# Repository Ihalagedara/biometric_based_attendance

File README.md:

# biometric_based_attendance_web_page
Open the main.html file to view the web page

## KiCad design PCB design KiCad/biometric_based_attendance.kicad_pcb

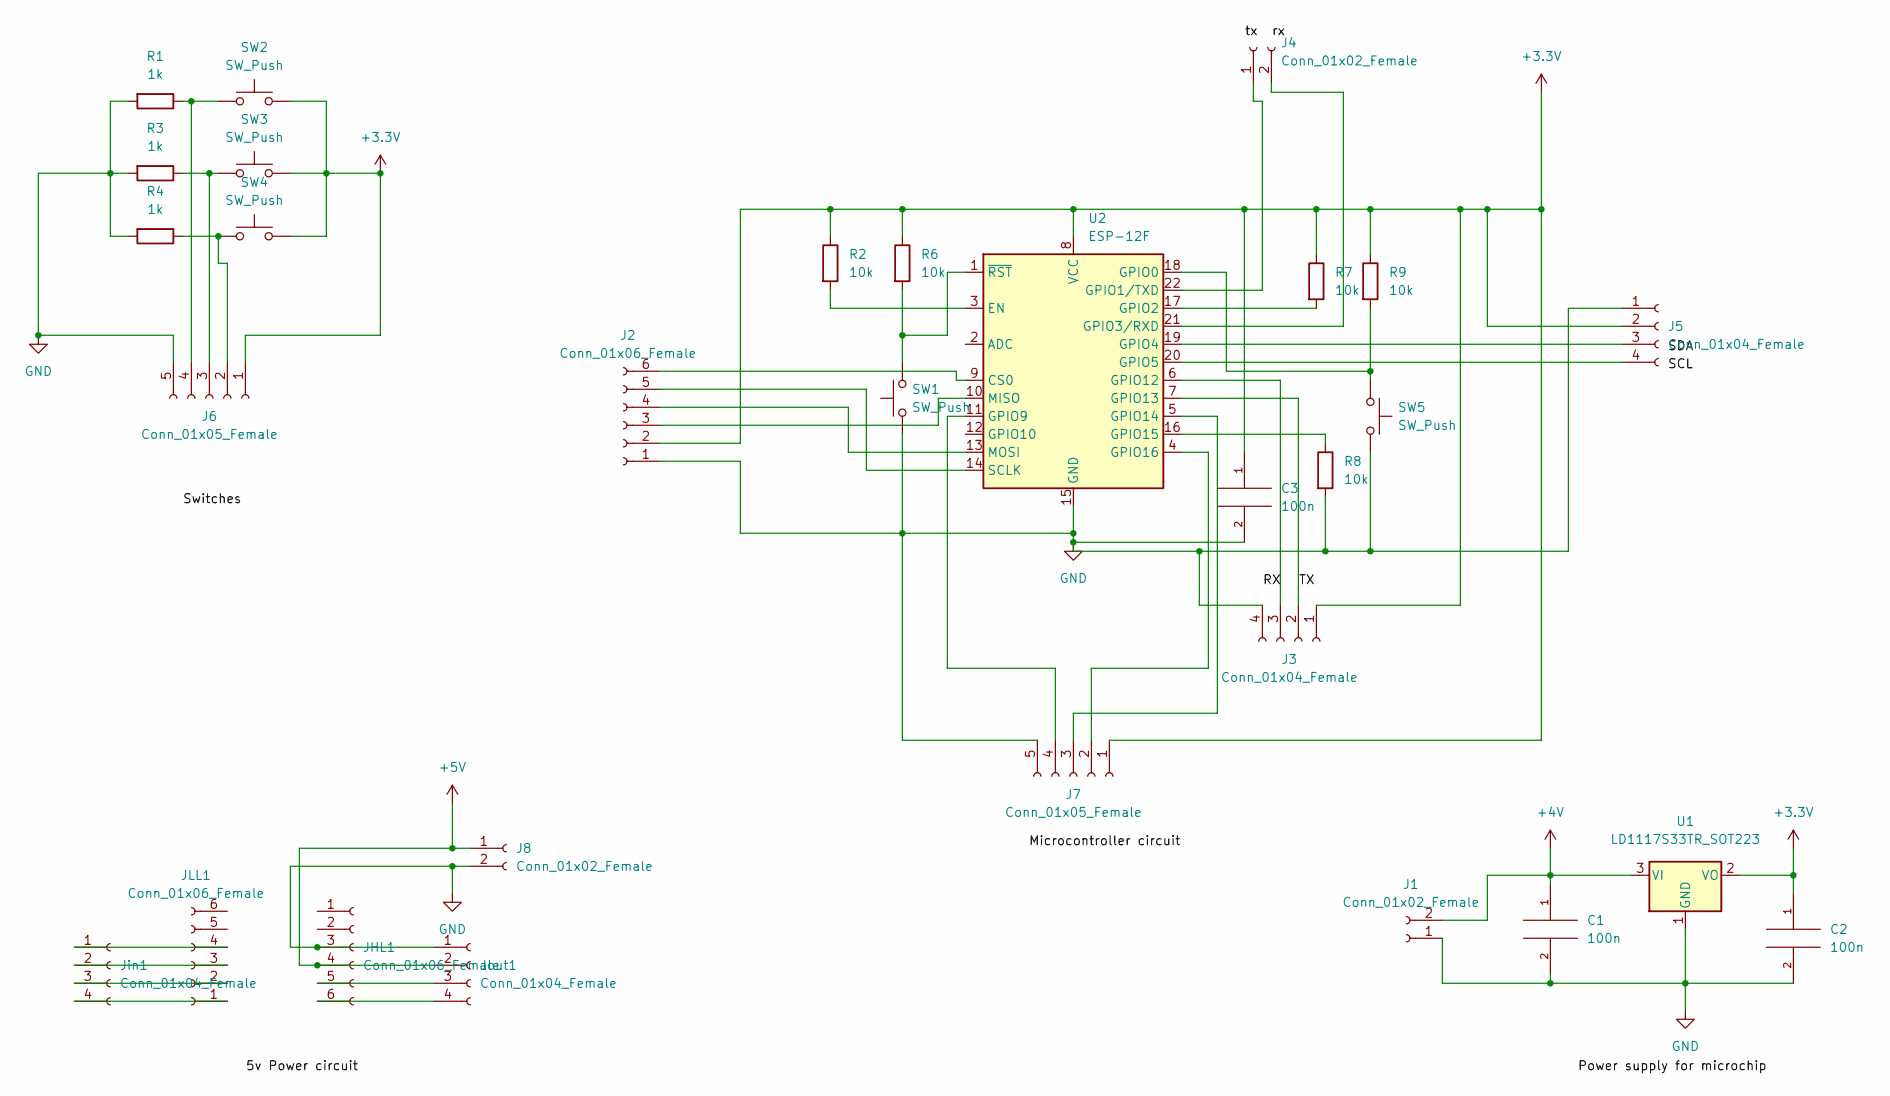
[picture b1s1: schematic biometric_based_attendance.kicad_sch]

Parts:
C1, C2, C3: 100n; C_Disc_D3.0mm_W1.6mm_P2.50mm
J1, J4, J8: Conn_01x02_Female; PinHeader_1x02_P2.54mm_Vertical
J2: Conn_01x06_Female; PinSocket_1x06_P2.54mm_Vertical
J3, J5: Conn_01x04_Female; PinSocket_1x04_P2.54mm_Vertical
J6, J7: Conn_01x05_Female; PinSocket_1x05_P2.54mm_Vertical
JHL1: Conn_01x06_Female; PinHeader_1x06_P2.54mm_Vertical
JLL1: Conn_01x06_Female; PinHeader_1x06_P2.54mm_Vertical
Jin1: Conn_01x04_Female; PinHeader_1x04_P2.54mm_Vertical
Jout1: Conn_01x04_Female; PinHeader_1x04_P2.54mm_Vertical
R1, R3, R4: 1k; R_Axial_DIN0204_L3.6mm_D1.6mm_P5.08mm_Horizontal
R2, R6, R7, R8, R9: 10k; R_Axial_DIN0204_L3.6mm_D1.6mm_P5.08mm_Horizontal
SW1, SW5: SW_Push; SW_PUSH_6mm
SW2, SW3, SW4: SW_Push; SW_PUSH_6mm_H13mm
U1: LD1117S33TR_SOT223; SOT-223-3_TabPin2
U2: ESP-12F; ESP-12E

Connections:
+3.3V: C2.1, C3.1, J2.2, J3.1, J5.2, J6.1, J7.1, R2.1, R6.1, R7.1, R9.1, SW2.2, SW3.2, SW4.2, U1.2 (VO), U2.8 (VCC)
+4V: C1.1, J1.2, U1.3 (VI)
+5V: J8.1, JHL1.4, Jout1.2
/TX: J3.2, U2.7 (GPIO13)
GND: C1.2, C2.2, C3.2, J1.1, J2.1, J3.4, J5.1, J6.5, J7.5, J8.2, JHL1.3, Jout1.1, R1.2, R3.2, R4.2, R8.2, SW1.1, SW5.2, U1.1 (GND), U2.15 (GND)
unnamed: J2.3, U2.10 (MISO)
unnamed: J2.4, U2.13 (MOSI)
unnamed: J2.5, U2.14 (SCLK)
unnamed: J2.6, U2.9 (CS0)
unnamed: J3.3, U2.6 (GPIO12)
unnamed: J4.1, U2.22 (GPIO1/TXD)
unnamed: J4.2, U2.21 (GPIO3/RXD)
unnamed: J5.3, U2.19 (GPIO4)
unnamed: J5.4, U2.20 (GPIO5)
unnamed: J6.2, R4.1, SW4.1
unnamed: J6.3, R3.1, SW3.1
unnamed: J6.4, R1.1, SW2.1
unnamed: J7.2, U2.4 (GPIO16)
unnamed: J7.3, U2.5 (GPIO14)
unnamed: J7.4, U2.11 (GPIO9)
unnamed: JHL1.5, Jout1.3
unnamed: JHL1.6, Jout1.4
unnamed: JLL1.1, Jin1.4
unnamed: JLL1.2, Jin1.3
unnamed: JLL1.3, Jin1.2
unnamed: JLL1.4, Jin1.1
unnamed: R2.2, U2.3 (EN)
unnamed: R6.2, SW1.2, U2.1 (~RST)
unnamed: R7.2, U2.17 (GPIO2)
unnamed: R8.1, U2.16 (GPIO15)
unnamed: R9.2, SW5.1, U2.18 (GPIO0)

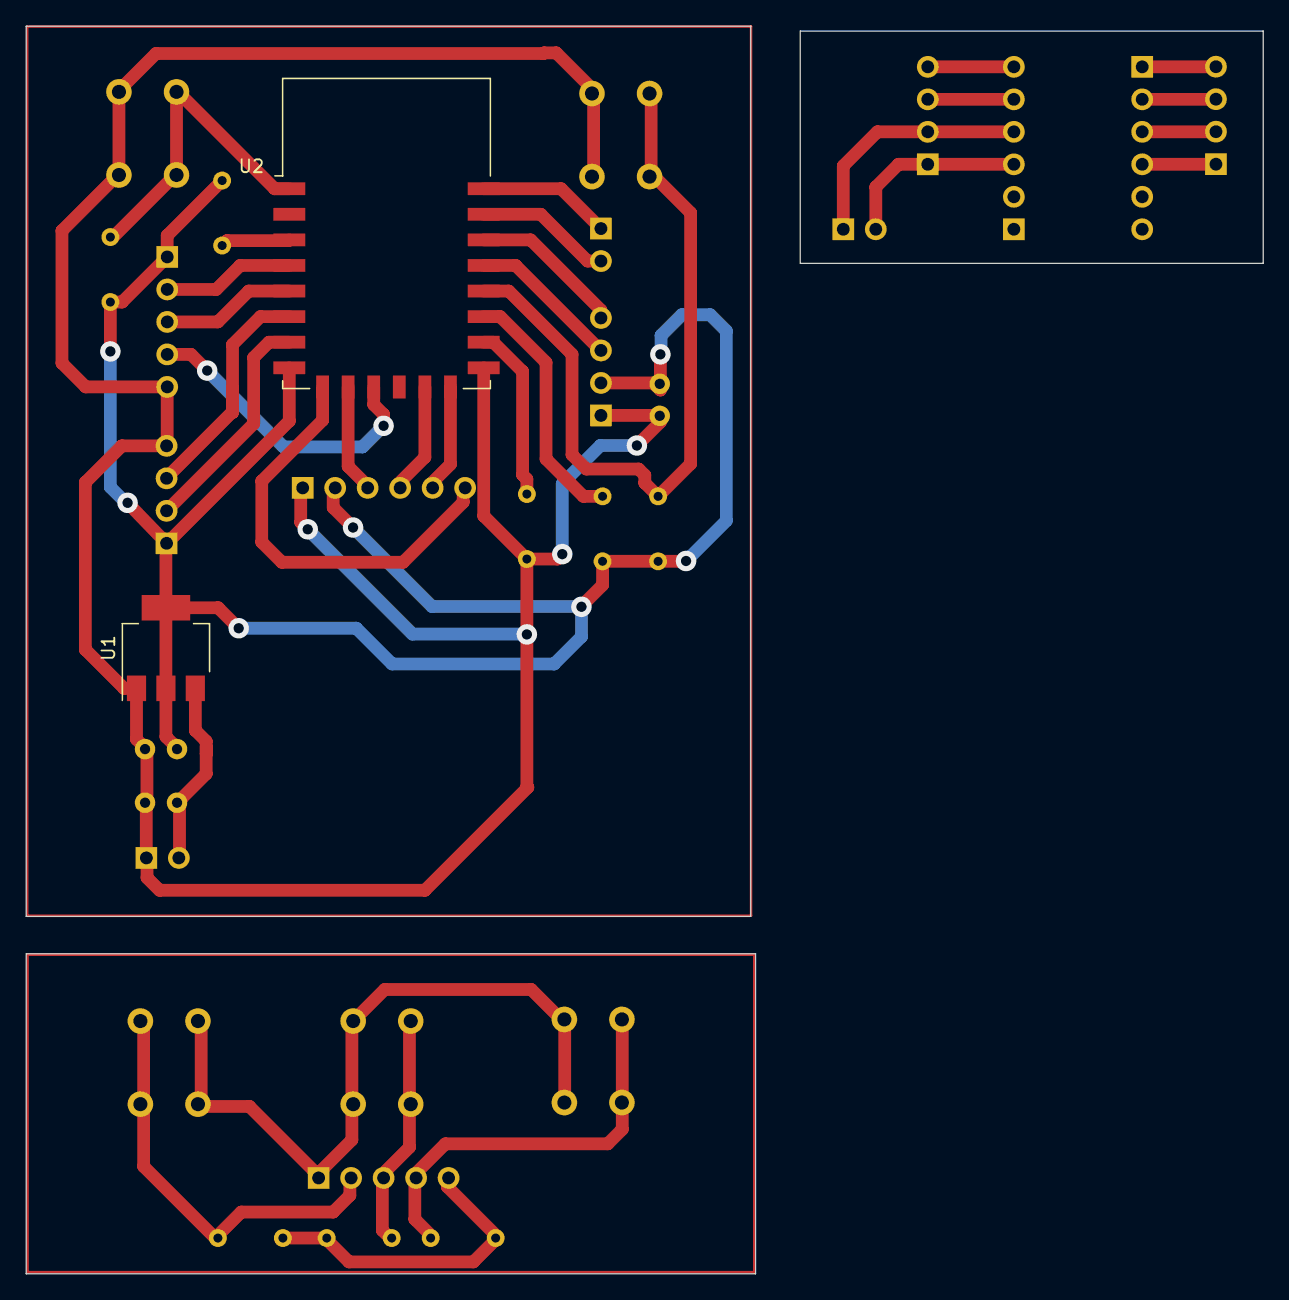
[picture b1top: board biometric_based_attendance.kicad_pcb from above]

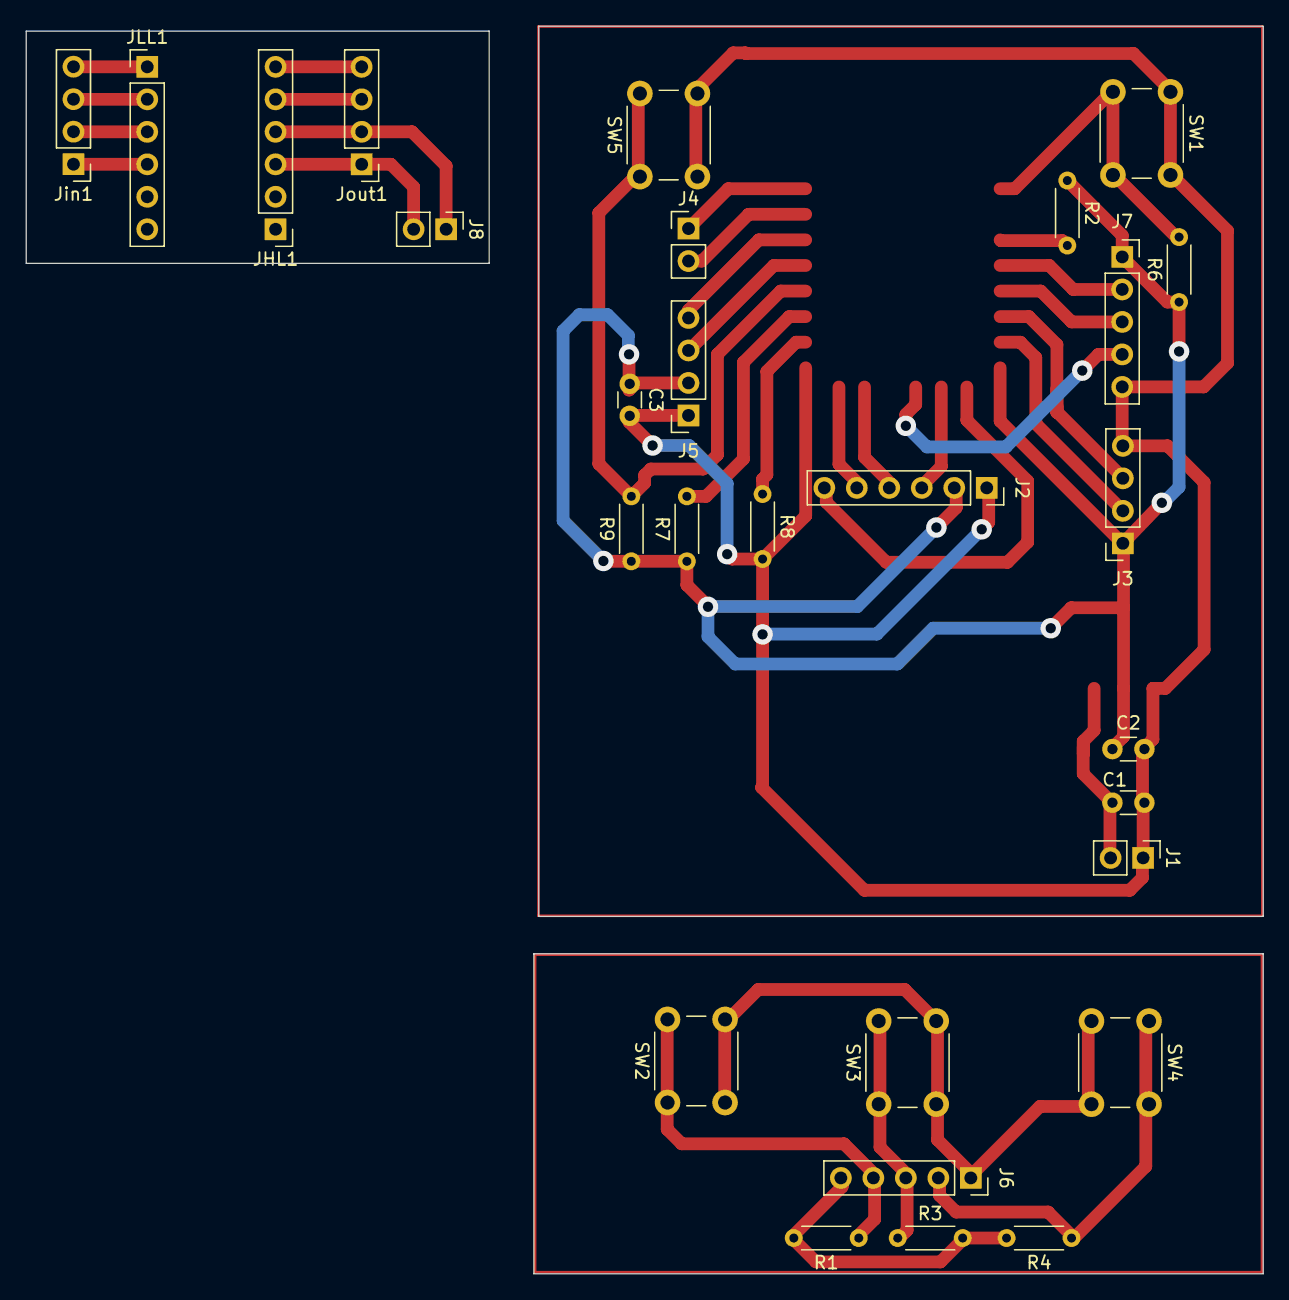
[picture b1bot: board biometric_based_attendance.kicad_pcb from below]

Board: 2 copper layers, 96.7 x 97.5 mm, 30 parts (28 on the bottom side), 31 nets.
